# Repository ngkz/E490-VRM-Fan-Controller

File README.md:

# ThinkPad E490 VRM Cooling Mod

- WIP
- Only for IGP model
- Maybe this mod also applicable to E590, E480, and E580

## How to flash the microcontroller
### Set fuse bits

```
$ pio run -t fuses
```

### Flash the firmware
```
$ pio run -t program
```

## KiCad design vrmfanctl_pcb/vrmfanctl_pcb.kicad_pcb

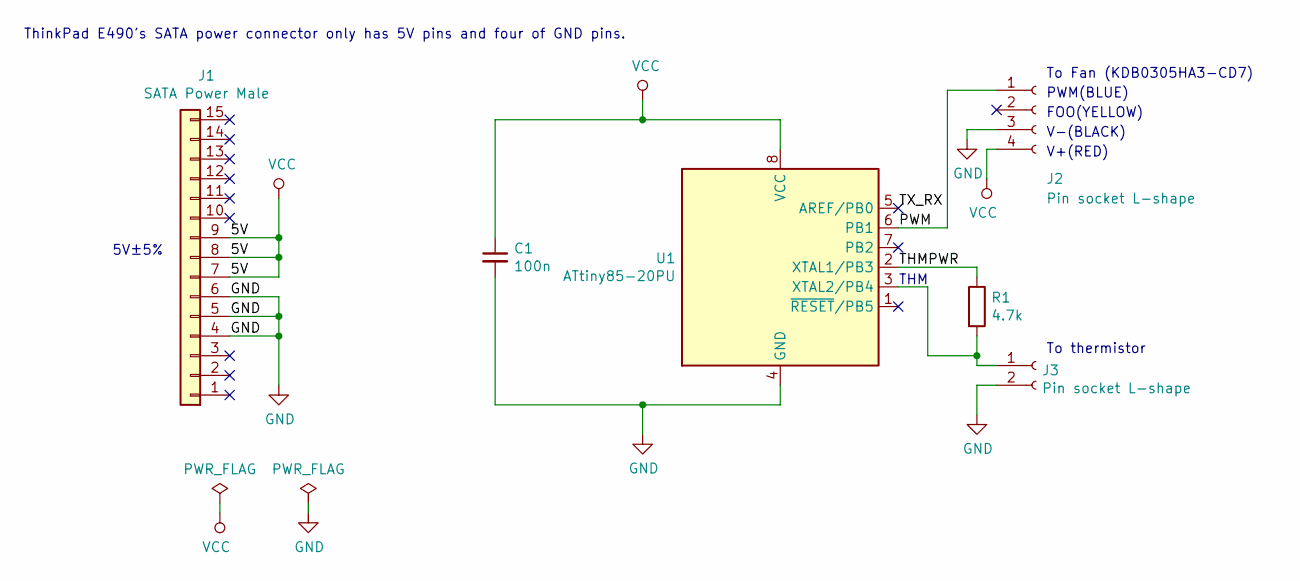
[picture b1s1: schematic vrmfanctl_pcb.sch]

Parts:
C1: 100n; C_Disc_D5.0mm_W2.5mm_P2.50mm
J1: SATA Power Male; SATA_Power_PCBEdge
J2: Pin socket L-shape; PinSocket_1x04_P2.54mm_Horizontal
J3: Pin socket L-shape; PinSocket_1x02_P2.54mm_Horizontal
R1: 4.7k; R_Axial_DIN0204_L3.6mm_D1.6mm_P5.08mm_Horizontal
U1: ATtiny85-20PU; DIP-8_W7.62mm

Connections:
/PWM: J2.1, U1.6 (PB1)
/THMPWR: R1.1, U1.2 (XTAL1/PB3)
/TX_RX: U1.5 (AREF/PB0)
GND: C1.2, J1.4, J1.5, J1.6, J2.3, J3.2, U1.4 (GND)
unnamed: J3.1, R1.2, U1.3 (XTAL2/PB4)
VCC: C1.1, J1.7, J1.8, J1.9, J2.4, U1.8 (VCC)

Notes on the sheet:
ThinkPad E490's SATA power connector only has 5V pins and four of GND pins.
PWM(BLUE)
FOO(YELLOW)
V-(BLACK)
V+(RED)
To Fan (KDB0305HA3-CD7)
5V±5%
To thermistor
THM

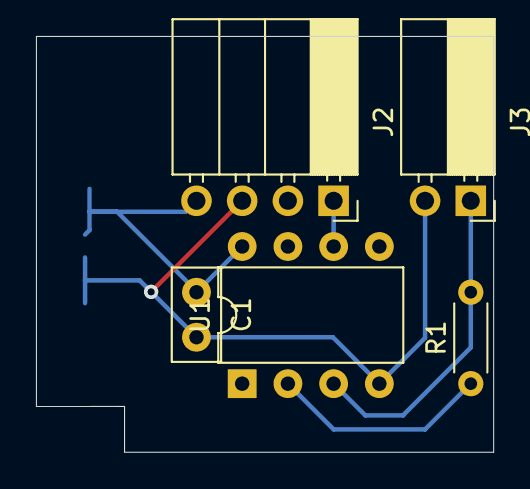
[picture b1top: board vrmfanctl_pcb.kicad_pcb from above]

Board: 2 copper layers, 25.4 x 23.1 mm, 6 parts (1 on the bottom side), 5 nets.

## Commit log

2019-07-26 reduce power consumption
2019-07-26 disable timer1 and timer0 at startup
2019-07-29 pull-up FG
2019-07-29 pwm control
2019-07-29 fuse comment
2019-07-30 configure Timer0 as a counter
2019-07-30 improve comment a bit
2019-07-30 measure fan rotation speed
2019-08-07 build with platformio
2019-08-07 refactor
2019-08-07 implement SMBus control interface
2019-08-08 implement duty register read
2019-08-09 remove unnecessary volatile
2019-08-09 remove duty register read
2019-08-09 scale duty to 0-255 -> 0-OCR1C
2019-08-09 improve comments
2019-08-09 rm .travis.yml
2019-08-09 add license header
2019-08-09 Add PCB and License file
2019-08-09 forgot to wire FG
2019-08-09 Use OC1A instead of OC1B. OC1B PWM output of ATTiny85 has a problem the same as ATTiny45 Rev B-C.
2019-08-09 turn off timer 1 when duty is 255
2019-08-09 return 0RPM if no FG signal over 1 second.
2019-08-10 disable analog comparator correctly
2019-08-10 add debug interface
2019-08-10 fix setFanDuty() bug
2019-08-10 it doesn't need a level shifter
2019-08-19 supply 3.3V with M.2 SSD
2019-08-21 Add a UART header. remove an I2C interface. Add a temperature sensor.
2019-08-21 use optiboot to upload the firmware
2019-08-21 Use through hole instead of pin header
2019-08-24 remove unneeded FG wire
2019-08-25 add firmware build instruction
2019-08-25 add reset pin to the header
2019-09-06 rewrite firmware and update pcb
2019-09-06 extract fan control loop
2019-09-08 refactor fan_control()
2019-09-08 add duty getter
2019-09-08 add static
2019-09-08 measure_vrm_temp->measure_temp, add ADC_VALUE_TO_VOLTAGE()
2019-09-10 change tachometer interface
2019-09-16 change tick
2019-09-16 make config global variable
2019-09-19 refactor and implement configuration interface
2019-09-19 fix a bug. startup_wait_remain -> fg_wait_remain
2019-09-19 add debug code
2019-09-19 update comment
2019-09-20 RX pin configuration was wrong
2019-09-20 fix a bug that the same register is allocated to ch and count.
2019-09-21 prevent that the optimization breaks software uart
2019-09-21 newline character is \r\n, not \n
2019-09-21 Read input from PINB, not PORTB
2019-09-21 Set fuses using platformio. Preserve EEPROM through the Cip Erase cycle. update README.
2019-09-21 stop erasing chip
2019-09-21 erase chip before uploading program
2019-09-21 treat \r as return
2019-09-21 make magic numbers macro. handle backspace correctly. send bell if the line buffer is full
2019-09-21 shorten trace output because UART is slow. increase baud rate. fix wrong timer 0 prescaler config.
2019-09-22 Fix integer overflow and underflow. ADC_VALUE_TO_VOLTAGE() -> adc_value_to_mv()
2019-09-22 make calibrate command cancellable
2019-09-22 change adc_diode_voltage() signedness
2019-09-22 make Config::zero_c_voltage float to improve thermometer precision
2019-09-22 round adc_value_to_mv(voltage)
2019-09-24 I don't know this applies to E590
2019-09-24 tidy up
2019-09-24 fix wrong zero_c_voltage calculation
2019-09-24 fix typo
2019-09-24 add workaround for ATTiny85 Timer Errata
2019-09-26 change pcb layout
2019-09-26 forgot to update PCINT_RX
2019-09-28 Stop using asynchronous timer because PLL consumes a lot of power. Increase system clock to 250kHz.
2019-09-28 improve trace output
2019-09-28 increase uart baud rate
2019-09-28 fix wrong fan duty range
2019-09-28 add set_fan_duty() test command
2019-09-28 show fan speed when testing fan
2019-09-29 change fan control algorithm
2019-09-29 remove tachometer and fantest command.
2019-09-29 remove unused config
2019-10-02 change temperature measurement method. remove configuration interface. use printf instead of put*.
2019-10-03 Squashed 'optiboot/' content from commit 35ba394
    git-subtree-dir: optiboot
    git-subtree-split: 35ba394479eb171ab77c24ec9abbb95a704043fe
2019-10-03 set OSCCAL
2019-10-03 Add ATtiny85 build target
2019-10-03 upload firmware with optiboot
2019-10-03 trace thermometer
2019-10-03 change fan control table
2019-10-03 simplify fan control algorithm
2019-10-04 change fan control threshold
2019-10-06 swap BDPWR10 and TX. Add UART pin header
2019-10-06 make uart half-duplex
2019-10-06 fix macro redefine warning
2019-10-06 ignore optiboot binaries
2019-10-07 replace optiboot with OWL
2019-10-07 \r\n
2019-10-07 debug ui
2019-10-07 forgot to commit debug.c
2019-10-07 fix uart clock
2019-10-07 fix debug ui
2019-10-07 fix wrong ELEMENTARY_CHANGE constant value
2019-10-07 convert temperature to celcius degree
2019-10-07 measure corrent ratio and idality factor
2019-10-08 add measure_temp() debug interface
2019-10-08 keep analog signals from digital signals
2019-10-08 enter adc noise reduction mode when a/d conversion
2019-10-08 swap PB2 and PB0
2019-10-08 recalculate ideality factor
2019-10-08 adc(): sample more
2019-10-14 use thermistor instead of thermal diode
2019-10-14 -Wall -Wextra -Werror
2019-10-14 calibrate adc. more accurate R1.
2019-10-15 remove bootloader. stop disabling reset pin. patch board definition with platformio.ini
2019-10-15 add more compile-time check
2019-10-15 remove debug ui. allow call TRACE() with one argument. increase system clock to 1MHz. remove oscillator calibration code. revert fan control algorithm. enter power-down mode if fan stopped. use wdt t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
2019-10-15 move configuration knobs to config.h.
2019-10-15 update pcb layout
2019-10-17 update thermistor config. change R1 resistor to 4.7K.
2019-10-17 change fan stop timing
2019-10-17 change trace timing
2019-10-19 make measure_temp() return type float
2019-10-19 take less samples when a/d conversion
2019-10-19 limit range of adc result
2019-10-19 prevent that measure_temp() return NaN if the thermistor is not connected
2019-10-19 change fan control parameter
